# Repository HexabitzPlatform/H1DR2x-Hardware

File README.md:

# H1DR2x-Hardware
Hexabitz CAN Transceiver Module Hardware Design

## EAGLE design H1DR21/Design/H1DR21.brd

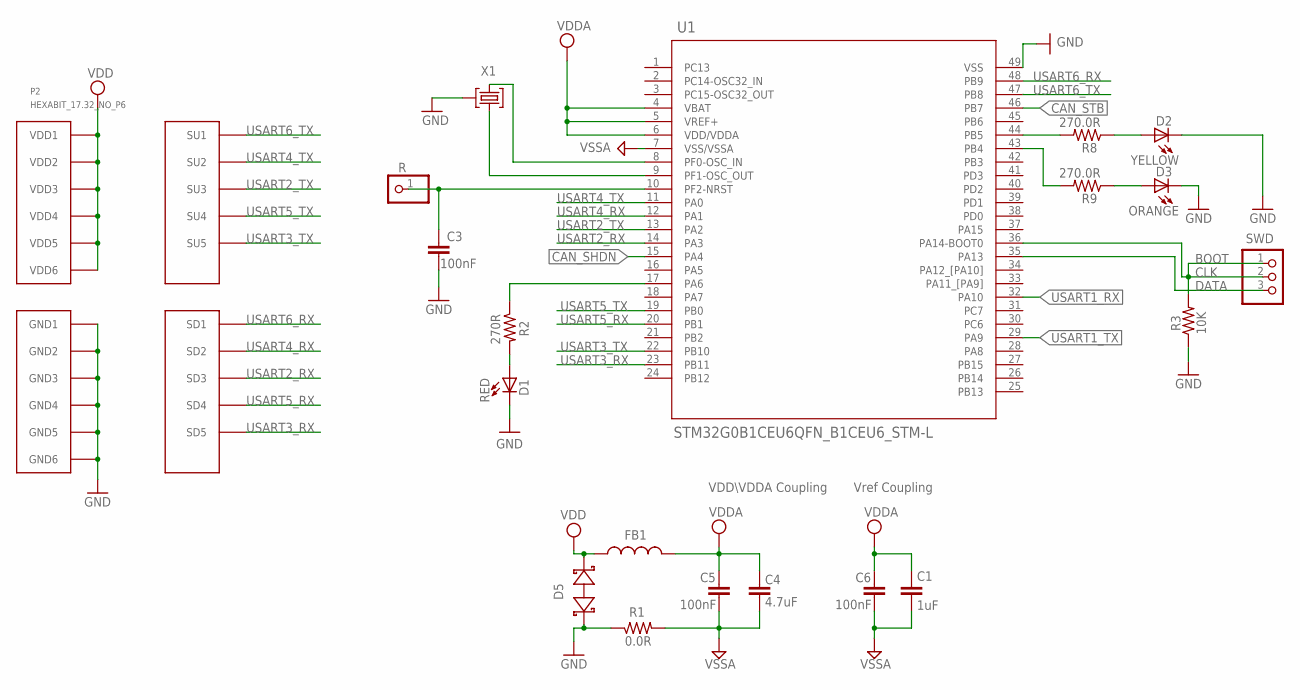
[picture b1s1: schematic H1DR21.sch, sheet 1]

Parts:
C1: 1uF; C-0805
C3, C5, C6: 100nF; C-0603
C4: 4.7uF; C-0805
D1: RED; VLMS1300-GS08; MPN VLMS1300-GS08
D2: YELLOW; VLMS1300-GS08
D3: ORANGE; VLMS1300-GS08
D5: BOURNS_CDSOD323-T03SCBOURNS_CDSOD323-T03SC_0_0; BOURNS_CDSOD323-T03SC_0
FB1: FB-TDK_MMZ1608Y300B; FB-0603; MPN MMZ1608Y300B
P2: HEXABIT_17.32_NO_P6
R: R; 1X01
R1: 0.0R; R-0603; MPN RC0603JR-070RL
R2: 270R; R-0603
R3: 10K; R-0603
R8, R9: 270.0R; R-0603
SWD: PINHD-1X3; 1X03
U1: STM32G0B1CEU6QFN_B1CEU6_STM-L; QFN_B1CEU6_STM-L
X1: XTALL_CSTCE8M00G52

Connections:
CAN_SHDN: U1.15 (PA4); also elsewhere on the board
CAN_STB: U1.46 (PB7); also elsewhere on the board
CLK: R3.2, SWD.1, SWD.2, U1.36 (PA14-BOOT0)
DATA: SWD.3, U1.35 (PA13)
GND: C3.2, D1.C, D2.C, D3.C, D5.1 (A), P2.PAD_PD7 (GND1), P2.PAD_PD8 (GND2), P2.PAD_PD9 (GND3), P2.PAD_PD10 (GND4), P2.PAD_PD11 (GND5), P2.PAD_PD12 (GND6), R1.1, R3.1, U1.49 (VSS), X1.P$2 (2); also elsewhere on the board
unnamed: D1.A, R2.2
unnamed: D3.A, R9.1
unnamed: R2.1, U1.17 (PA6)
unnamed: C3.1, R.1, U1.10 (PF2-NRST)
unnamed: U1.9 (PF1-OSC_OUT), X1.P$1 (1)
unnamed: U1.8 (PF0-OSC_IN), X1.P$3 (3)
unnamed: D2.A, R8.1
unnamed: R8.2, U1.44 (PB5)
unnamed: R9.2, U1.43 (PB4)
USART1_RX: U1.32 (PA10); also elsewhere on the board
USART1_TX: U1.29 (PA9); also elsewhere on the board
USART2_RX: P2.PAD_PD3 (SD3), U1.14 (PA3)
USART2_TX: P2.PAD_PU3 (SU3), U1.13 (PA2)
USART3_RX: P2.PAD_PD5 (SD5), U1.23 (PB11)
USART3_TX: P2.PAD_PU5 (SU5), U1.22 (PB10)
USART4_RX: P2.PAD_PD2 (SD2), U1.12 (PA1)
USART4_TX: P2.PAD_PU2 (SU2), U1.11 (PA0)
USART5_RX: P2.PAD_PD4 (SD4), U1.20 (PB1)
USART5_TX: P2.PAD_PU4 (SU4), U1.19 (PB0)
USART6_RX: P2.PAD_PD1 (SD1), U1.48 (PB9)
USART6_TX: P2.PAD_PU1 (SU1), U1.47 (PB8)
VDD: D5.2 (C), FB1.2, P2.PAD_PU7 (VDD1), P2.PAD_PU8 (VDD2), P2.PAD_PU9 (VDD3), P2.PAD_PU10 (VDD4), P2.PAD_PU11 (VDD5), P2.PAD_PU12 (VDD6); also elsewhere on the board
VDDA: C1.1, C4.1, C5.1, C6.1, FB1.1, U1.4 (VBAT), U1.5 (VREF+), U1.6 (VDD/VDDA)
VSSA: C1.2, C4.2, C5.2, C6.2, R1.2, U1.7 (VSS/VSSA)

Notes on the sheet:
Vref Coupling
VDD\VDDA Coupling
BOOT

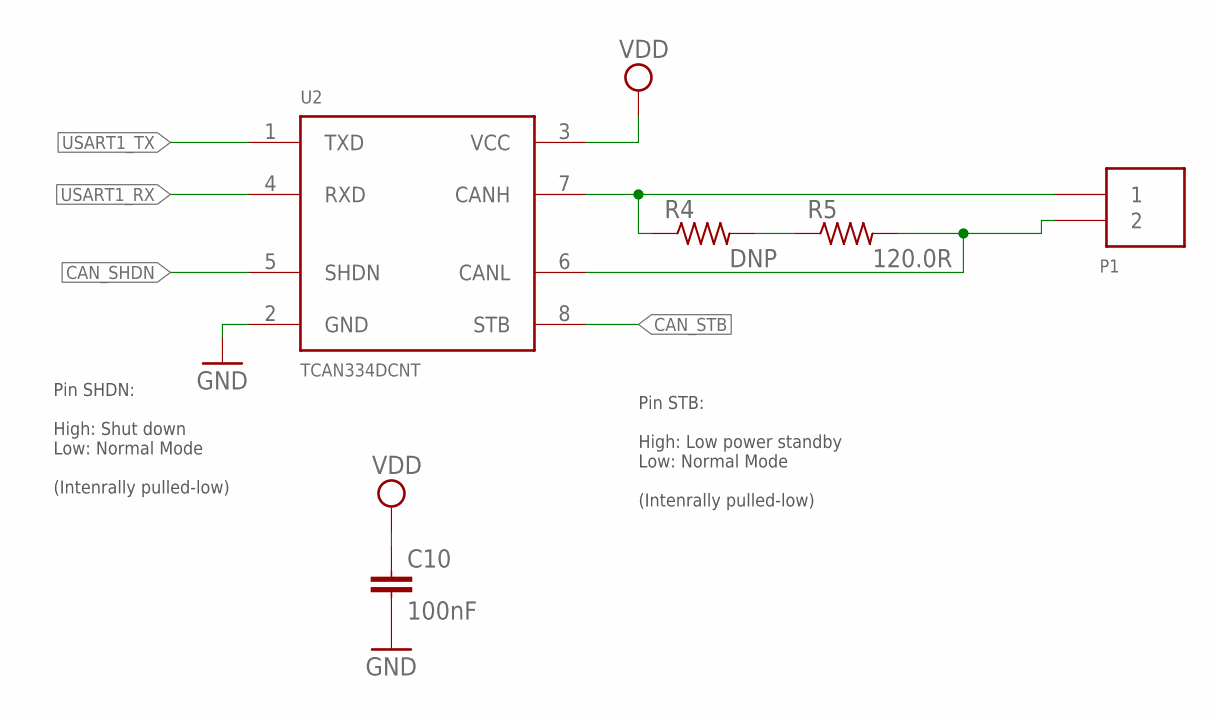
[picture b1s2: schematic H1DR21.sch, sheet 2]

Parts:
C10: 100nF; C-0603; TOLERANCE 10%; VOLTAGE_RATING 10V; MPN C0603C104K8RACTU
P1: 1546111-2
R4: DNP; R-0603; MPN RC0603JR-070RL
R5: 120.0R; R-0603; TOLERANCE 1%; MPN AC0603FR-07120RL
U2: TCAN334DCNT

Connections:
CAN_SHDN: U2.5 (SHDN); also elsewhere on the board
CAN_STB: U2.8 (STB); also elsewhere on the board
GND: C10.2, U2.2 (GND); also elsewhere on the board
unnamed: P1.1, R4.1, U2.7 (CANH)
unnamed: R4.2, R5.1
unnamed: P1.2, R5.2, U2.6 (CANL)
USART1_RX: U2.4 (RXD); also elsewhere on the board
USART1_TX: U2.1 (TXD); also elsewhere on the board
VDD: C10.1, U2.3 (VCC); also elsewhere on the board

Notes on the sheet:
Pin SHDN: High: Shut down Low: Normal Mode (Intenrally pulled-low)
Pin STB: High: Low power standby Low: Normal Mode (Intenrally pulled-low)

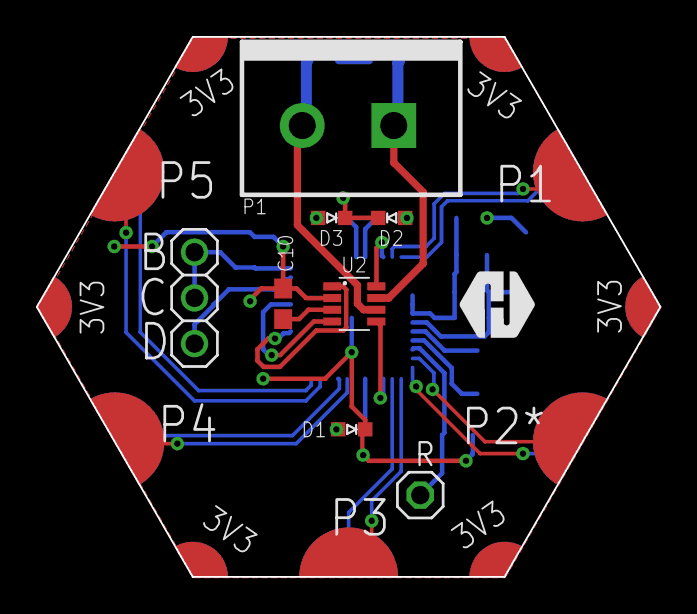
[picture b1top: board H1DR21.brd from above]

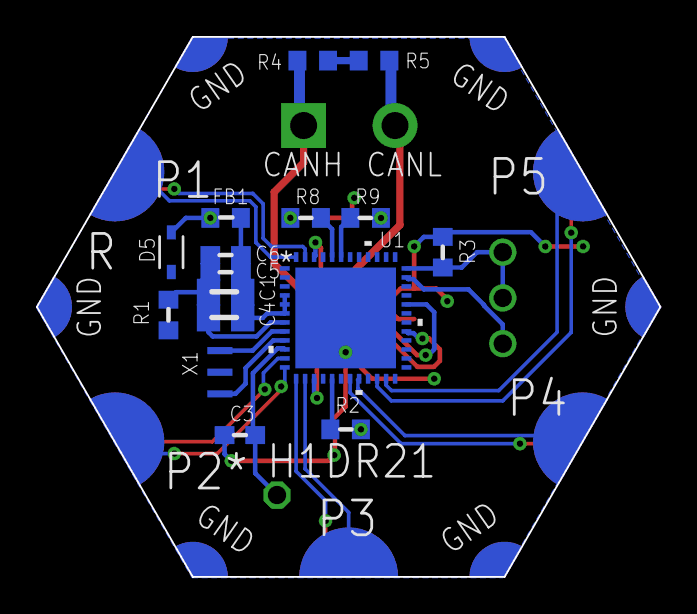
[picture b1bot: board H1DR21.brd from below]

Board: 2 copper layers, 34.6 x 30.0 mm, 26 parts (16 on the bottom side), 32 nets.

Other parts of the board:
U$1: HEXA-LOGO

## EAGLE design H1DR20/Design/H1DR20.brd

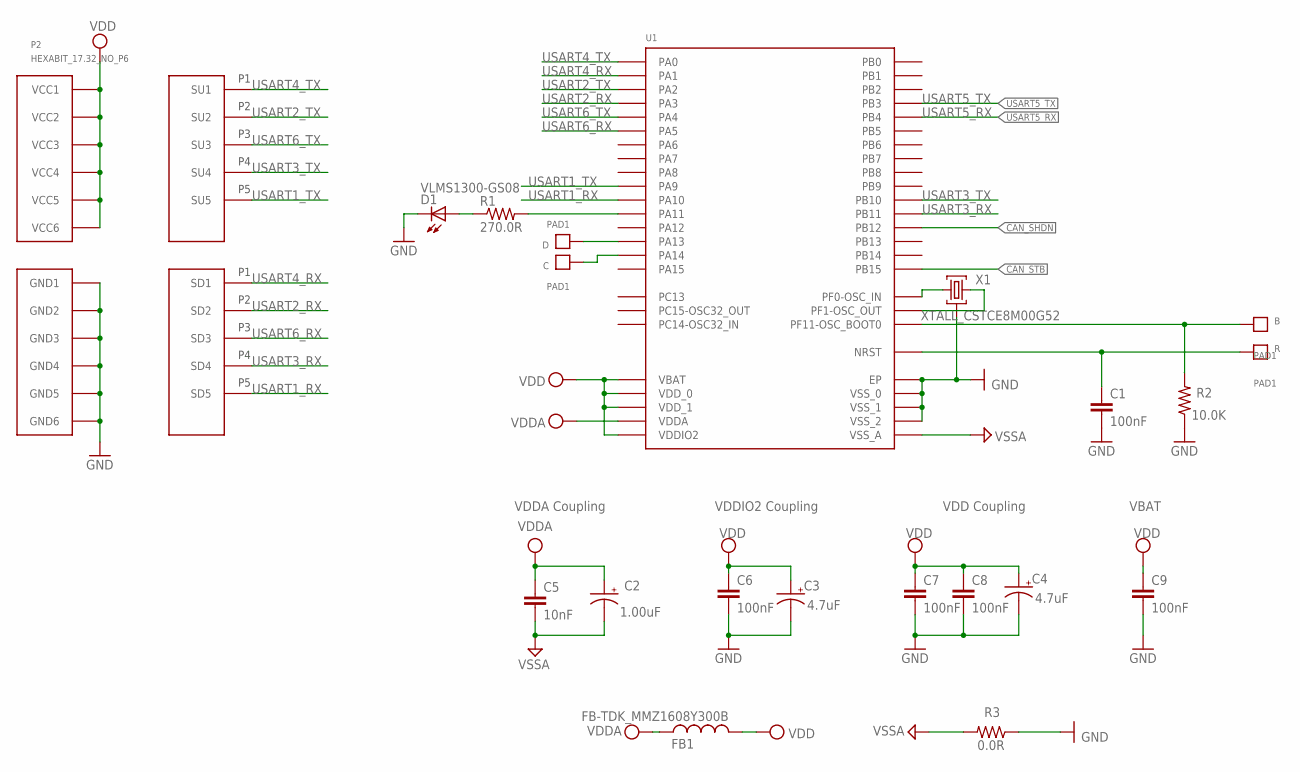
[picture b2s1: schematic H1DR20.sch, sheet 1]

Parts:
B: PAD1
C: PAD1
C1, C6, C8: 100nF; C-0603; TOLERANCE 10%; VOLTAGE_RATING 10V; MPN C0603C104K8RACTU
C2: 1.00uF; C-0805-POL; TOLERANCE 10%; VOLTAGE_RATING 16V; MPN CC0805KKX7R7BB105
C3, C4: 4.7uF; C-0805-POL; TOLERANCE 10%; VOLTAGE_RATING 25V; MPN GRM21BC81E475KA12L
C5: 10nF; C-0603; TOLERANCE 10%; VOLTAGE_RATING 50V; MPN C0603C103K5RACTU
C7: 100nF; C-0603; TOLERANCE 10%; VOLTAGE_RATING 10; MPN C0603C104K8RACTU
C9: 100nF; C-0603; TOLERANCE 10V; VOLTAGE_RATING 10%; MPN C0603C104K8RACTU
D: PAD1
D1: VLMS1300-GS08; MPN VLMS1300-GS08
FB1: FB-TDK_MMZ1608Y300B; MPN MMZ1608Y300B
P2: HEXABIT_17.32_NO_P6
R: PAD1
R1: 270.0R; R-0603; TOLERANCE 1%; MPN RC0603FR-07270RL
R2: 10.0K; R-0603; TOLERANCE 5%; MPN RC0603JR-0710KL
R3: 0.0R; R-0603; MPN RC0603JR-070RL
U1: STM32F091CBU6
X1: XTALL_CSTCE8M00G52

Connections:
B: B.P$1, B.P$2, R2.2, U1.P$44 (PF11-OSC_BOOT0)
CAN_SHDN: U1.P$25 (PB12); also elsewhere on the board
CAN_STB: U1.P$28 (PB15); also elsewhere on the board
GND: C1.2, C3.2 (-), C4.2 (-), C6.2, C7.2, C8.2, C9.2, D1.C, P2.7 (GND1), P2.8 (GND2), P2.9 (GND3), P2.10 (GND4), P2.11 (GND5), P2.12 (GND6), R2.1, R3.1, U1.EP, U1.P$23 (VSS_0), U1.P$35 (VSS_1), U1.P$47 (VSS_2), X1.P$2 (2); also elsewhere on the board
unnamed: D.P$1, D.P$2, U1.P$34 (PA13)
unnamed: C.P$1, C.P$2, U1.P$37 (PA14)
unnamed: R1.2, U1.P$32 (PA11)
unnamed: D1.A, R1.1
unnamed: U1.P$5 (PF0-OSC_IN), X1.P$1 (1)
unnamed: U1.P$6 (PF1-OSC_OUT), X1.P$3 (3)
R: C1.1, R.P$1, R.P$2, U1.P$7 (NRST)
USART1_RX: P2.23 (SD5), U1.P$31 (PA10)
USART1_TX: P2.17 (SU5), U1.P$30 (PA9)
USART2_RX: P2.20 (SD2), U1.P$13 (PA3)
USART2_TX: P2.14 (SU2), U1.P$12 (PA2)
USART3_RX: P2.22 (SD4), U1.P$22 (PB11)
USART3_TX: P2.16 (SU4), U1.P$21 (PB10)
USART4_RX: P2.19 (SD1), U1.P$11 (PA1)
USART4_TX: P2.13 (SU1), U1.P$10 (PA0)
USART5_RX: U1.P$40 (PB4); also elsewhere on the board
USART5_TX: U1.P$39 (PB3); also elsewhere on the board
USART6_RX: P2.21 (SD3), U1.P$15 (PA5)
USART6_TX: P2.15 (SU3), U1.P$14 (PA4)
VDD: C3.1 (+), C4.1 (+), C6.1, C7.1, C8.1, C9.1, FB1.2, P2.1 (VCC1), P2.2 (VCC2), P2.3 (VCC3), P2.4 (VCC4), P2.5 (VCC5), P2.6 (VCC6), U1.P$1 (VBAT), U1.P$24 (VDD_0), U1.P$36 (VDDIO2), U1.P$48 (VDD_1); also elsewhere on the board
VDDA: C2.1 (+), C5.1, FB1.1, U1.P$9 (VDDA)
VSSA: C2.2 (-), C5.2, R3.2, U1.P$8 (VSS_A)

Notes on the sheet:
VDDA Coupling
VDDIO2 Coupling
VDD Coupling
VBAT

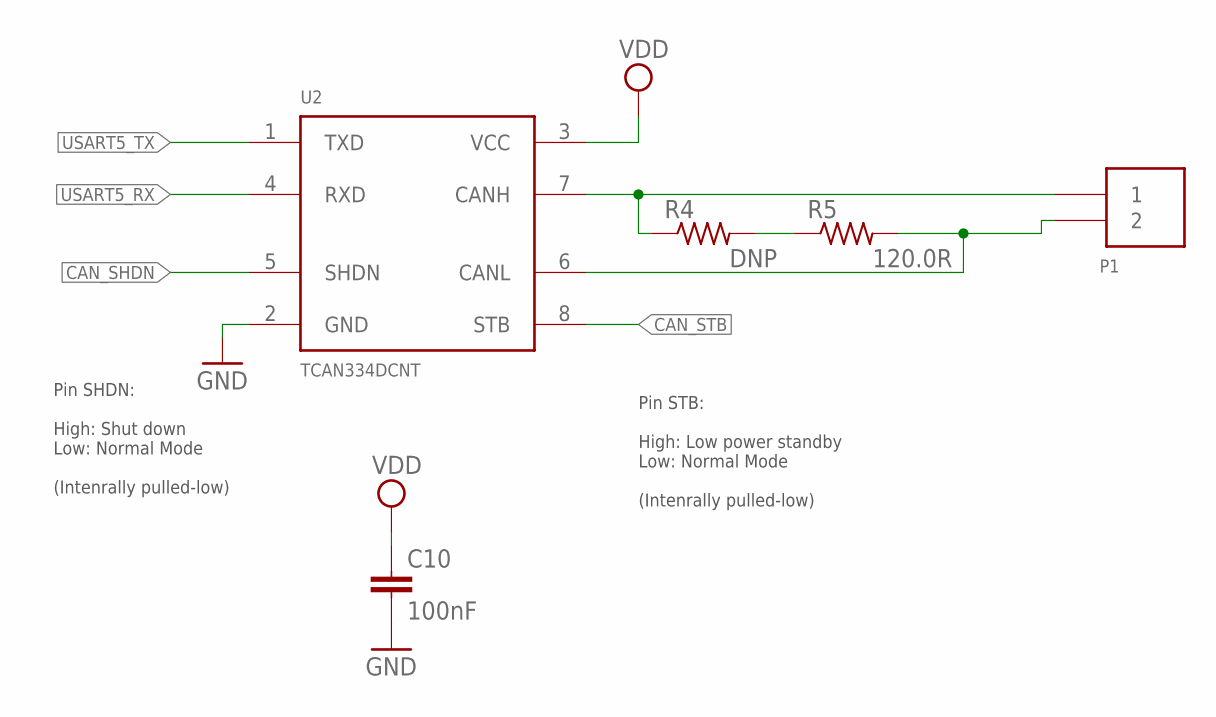
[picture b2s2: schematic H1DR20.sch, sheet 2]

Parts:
C10: 100nF; C-0603; TOLERANCE 10%; VOLTAGE_RATING 10V; MPN C0603C104K8RACTU
P1: 1546111-2
R4: DNP; R-0603; MPN RC0603JR-070RL
R5: 120.0R; R-0603; TOLERANCE 1%; MPN AC0603FR-07120RL
U2: TCAN334DCNT

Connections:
CAN_SHDN: U2.5 (SHDN); also elsewhere on the board
CAN_STB: U2.8 (STB); also elsewhere on the board
GND: C10.2, U2.2 (GND); also elsewhere on the board
unnamed: P1.1, R4.1, U2.7 (CANH)
unnamed: R4.2, R5.1
unnamed: P1.2, R5.2, U2.6 (CANL)
USART5_RX: U2.4 (RXD); also elsewhere on the board
USART5_TX: U2.1 (TXD); also elsewhere on the board
VDD: C10.1, U2.3 (VCC); also elsewhere on the board

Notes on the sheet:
Pin SHDN: High: Shut down Low: Normal Mode (Intenrally pulled-low)
Pin STB: High: Low power standby Low: Normal Mode (Intenrally pulled-low)

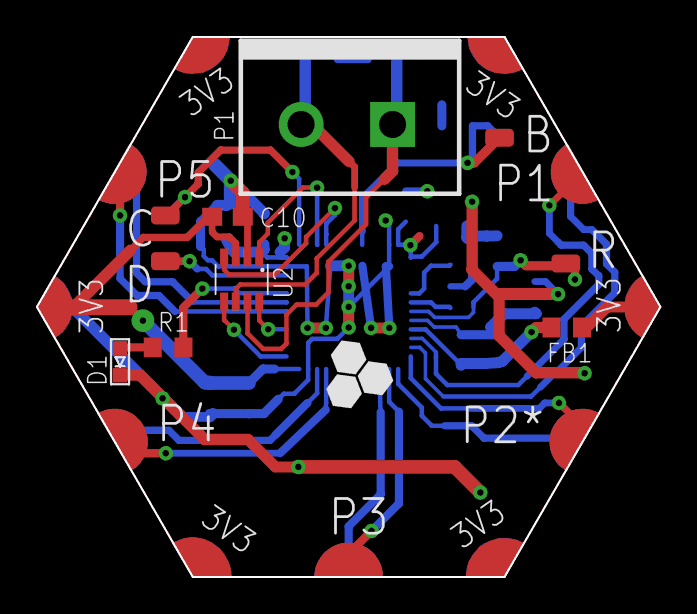
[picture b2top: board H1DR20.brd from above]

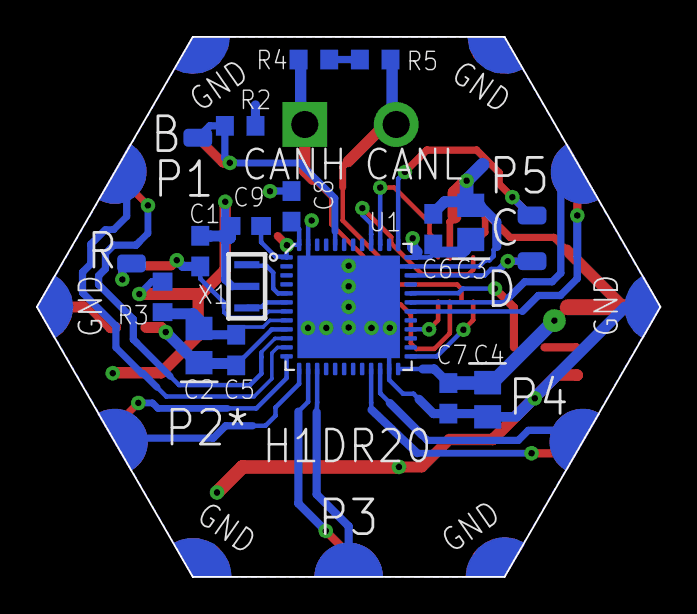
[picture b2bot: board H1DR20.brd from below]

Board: 2 copper layers, 34.6 x 30.0 mm, 26 parts (15 on the bottom side), 29 nets.

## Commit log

2019-05-23 First release rev 0
2024-12-11 - Changed MCU to G0 - New schematic design - New Layout - Generated documentation - Generated BOM - Deleted old output files (drills, gerber, pick and place)
2024-12-12 - Changed USART routes width to 8mil
2024-12-14 - Rearranged components in BOM
2024-12-14 - Changed logo in layout - Rearranged components in BOM

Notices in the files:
parts and their libraries:
COPYRIGHT: Copyright (C) 2021 Ultra Librarian. All rights reserved.
